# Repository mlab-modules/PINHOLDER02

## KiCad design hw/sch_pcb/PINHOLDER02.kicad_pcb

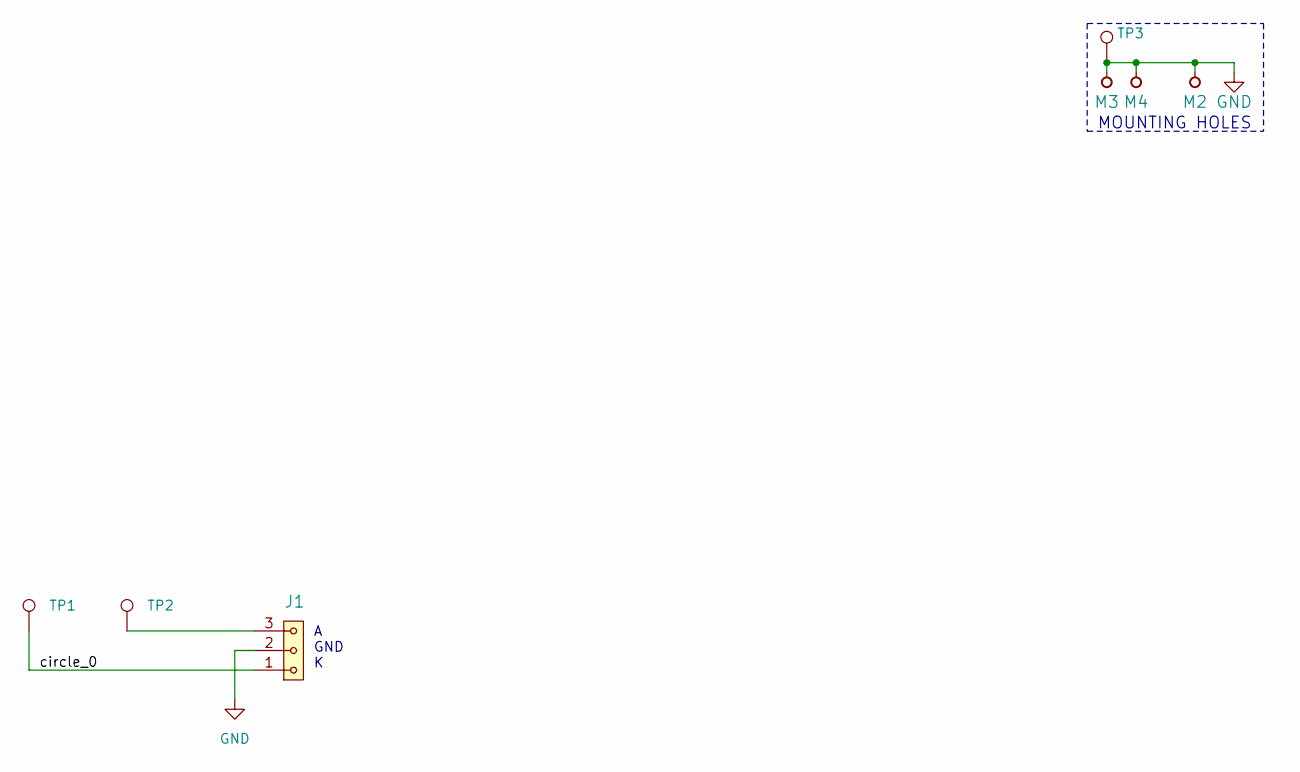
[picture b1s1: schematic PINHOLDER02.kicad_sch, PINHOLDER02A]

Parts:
J1: HEADER_1x03; PinHeader_1x03_P2.54mm_Vertical_SMD_Pin1Left
M2, M3, M4: HOLE; MountingHole_3mm
TP1, TP2, TP3: TestPoint; TestPoint_Pad_D0.5mm_noSilk

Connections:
/circle_0: J1.1, TP1.1
GND: J1.2, M2.1, M3.1, M4.1, TP3.1
unnamed: J1.3, TP2.1

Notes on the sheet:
MOUNTING HOLES
A GND K

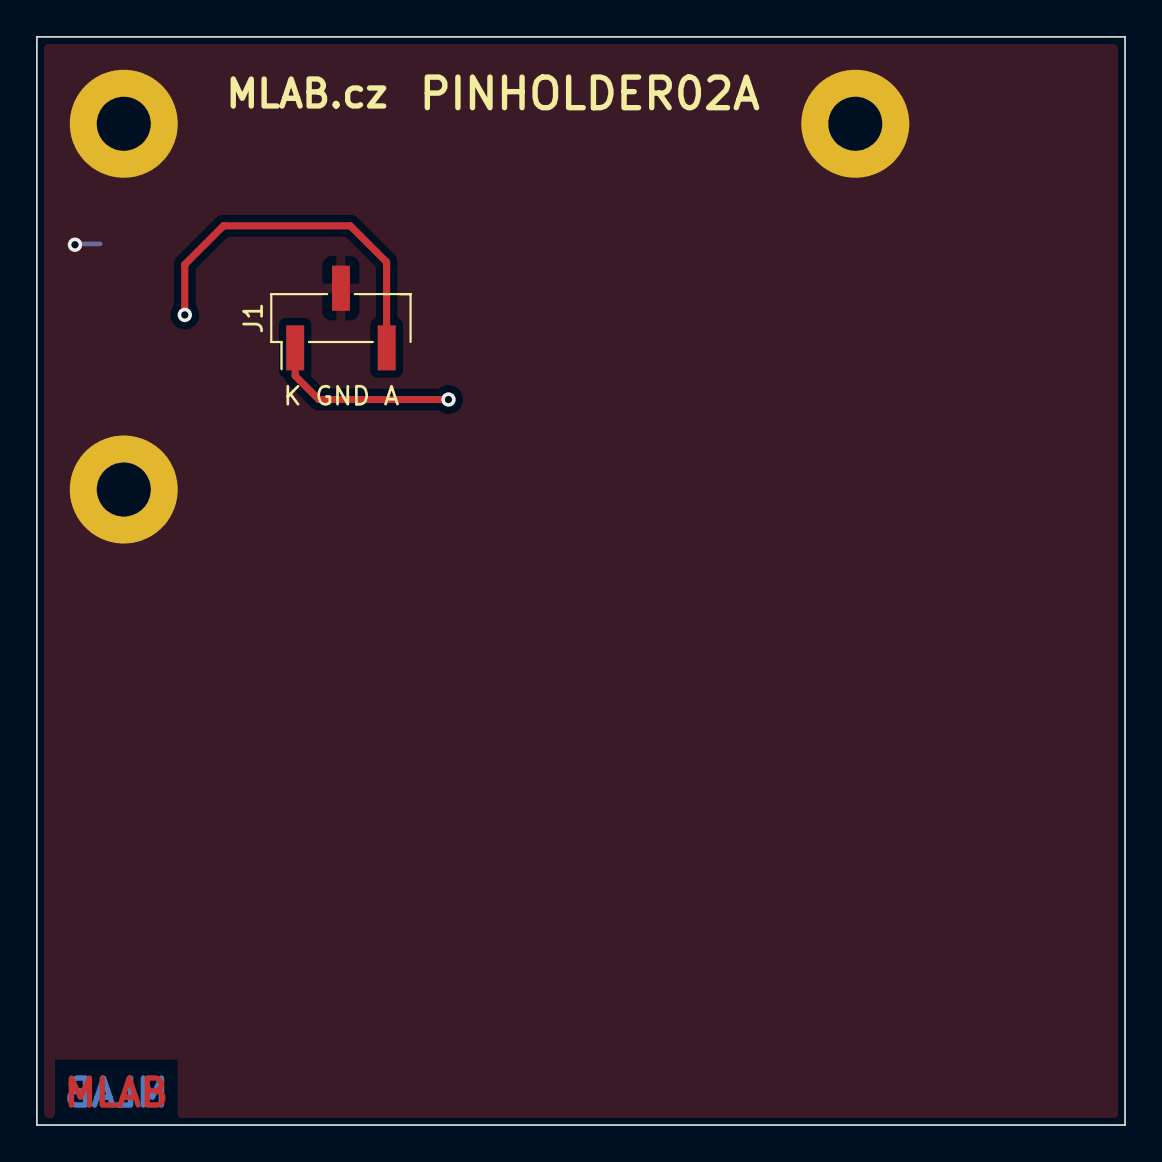
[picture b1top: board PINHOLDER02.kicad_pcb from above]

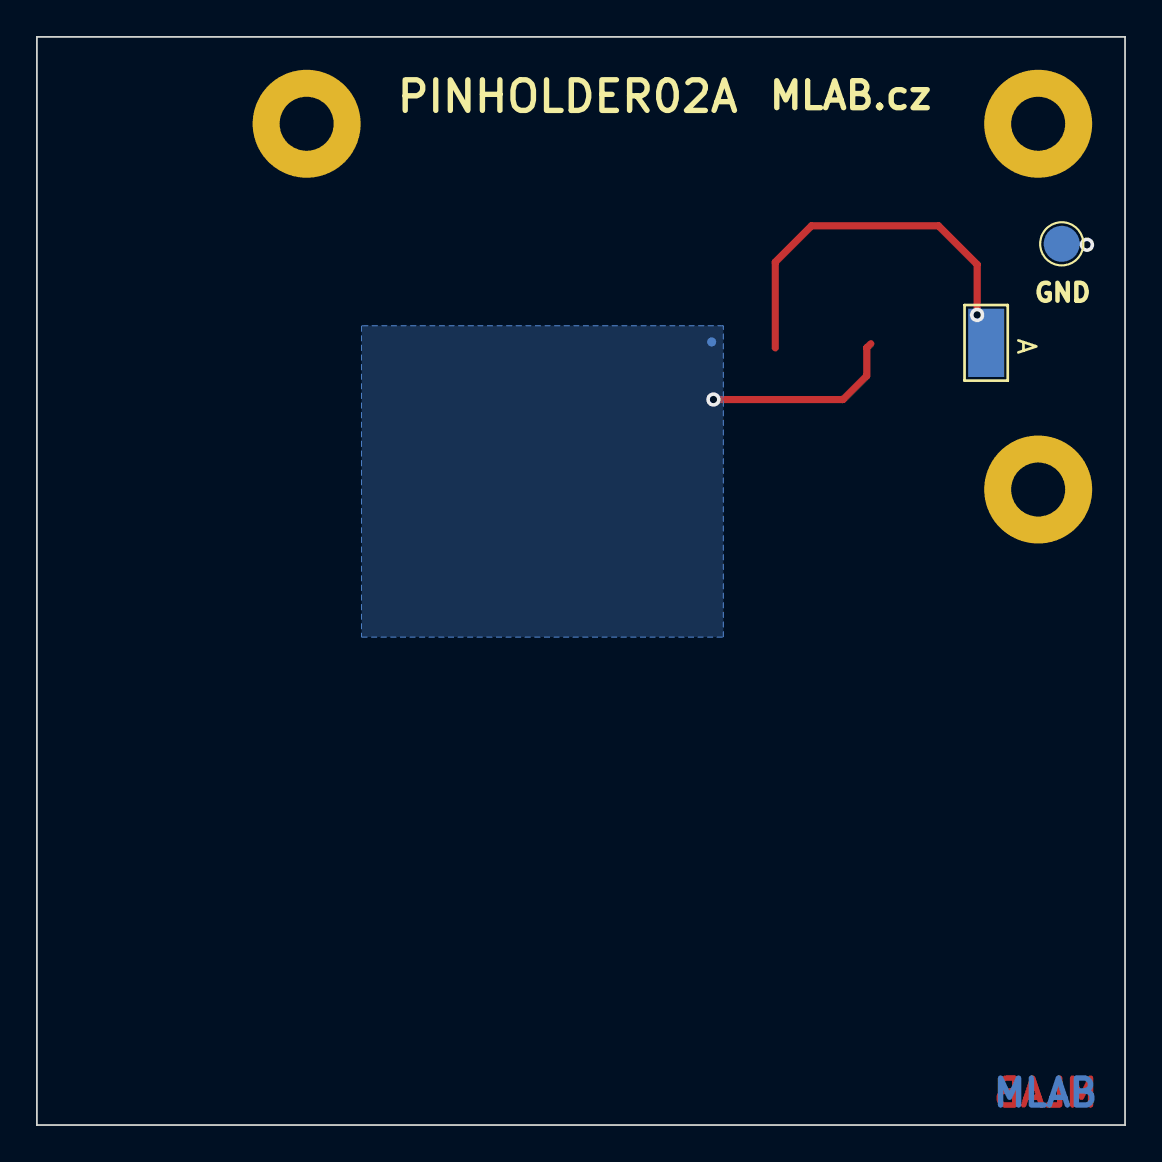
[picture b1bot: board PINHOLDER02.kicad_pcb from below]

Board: 2 copper layers, 60.5 x 60.5 mm, 7 parts (3 on the bottom side), 3 nets.

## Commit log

2023-04-12 Cleanup layout. copy name to bottom.
2023-04-13 uprava layoutu pro velkou diodu
2023-04-13 zamena anoda-katoda
2023-04-13 schematics anotate
2023-04-13 Fix shape to be ortogonal.
2023-04-13 Edit PCB
2023-04-13 Update metadata files
2023-04-13 Update actions products
2023-04-13 Run drc checks.
2023-04-13 Set specific units for dimensions suppress zeros.
2023-04-13 update assets
2023-04-14 Update workflow files
2023-05-28 automated commit; add github actions
2023-07-05 automated commit; rename source files to new naming convence
2023-09-16 Update image to image_title
2023-09-16 Update status
